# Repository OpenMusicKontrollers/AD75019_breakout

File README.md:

# AD75019 breakout

## About
This is the PCB design of a breakout board for
[Analog Devices](http://www.analog.com)
[AD75019](http://www.analog.com/en/switchesmultiplexers/analog-crosspoint-switches/ad75019/products/product.html) 16x16 analog crosspoint switch.

## Prerequisites
To be used with [KiCAD](http://www.kicad-pcb.org).

## License
This is open source hardware and licensed under [CERN OHL v.1.2](http://ohwr.org/cernohl).

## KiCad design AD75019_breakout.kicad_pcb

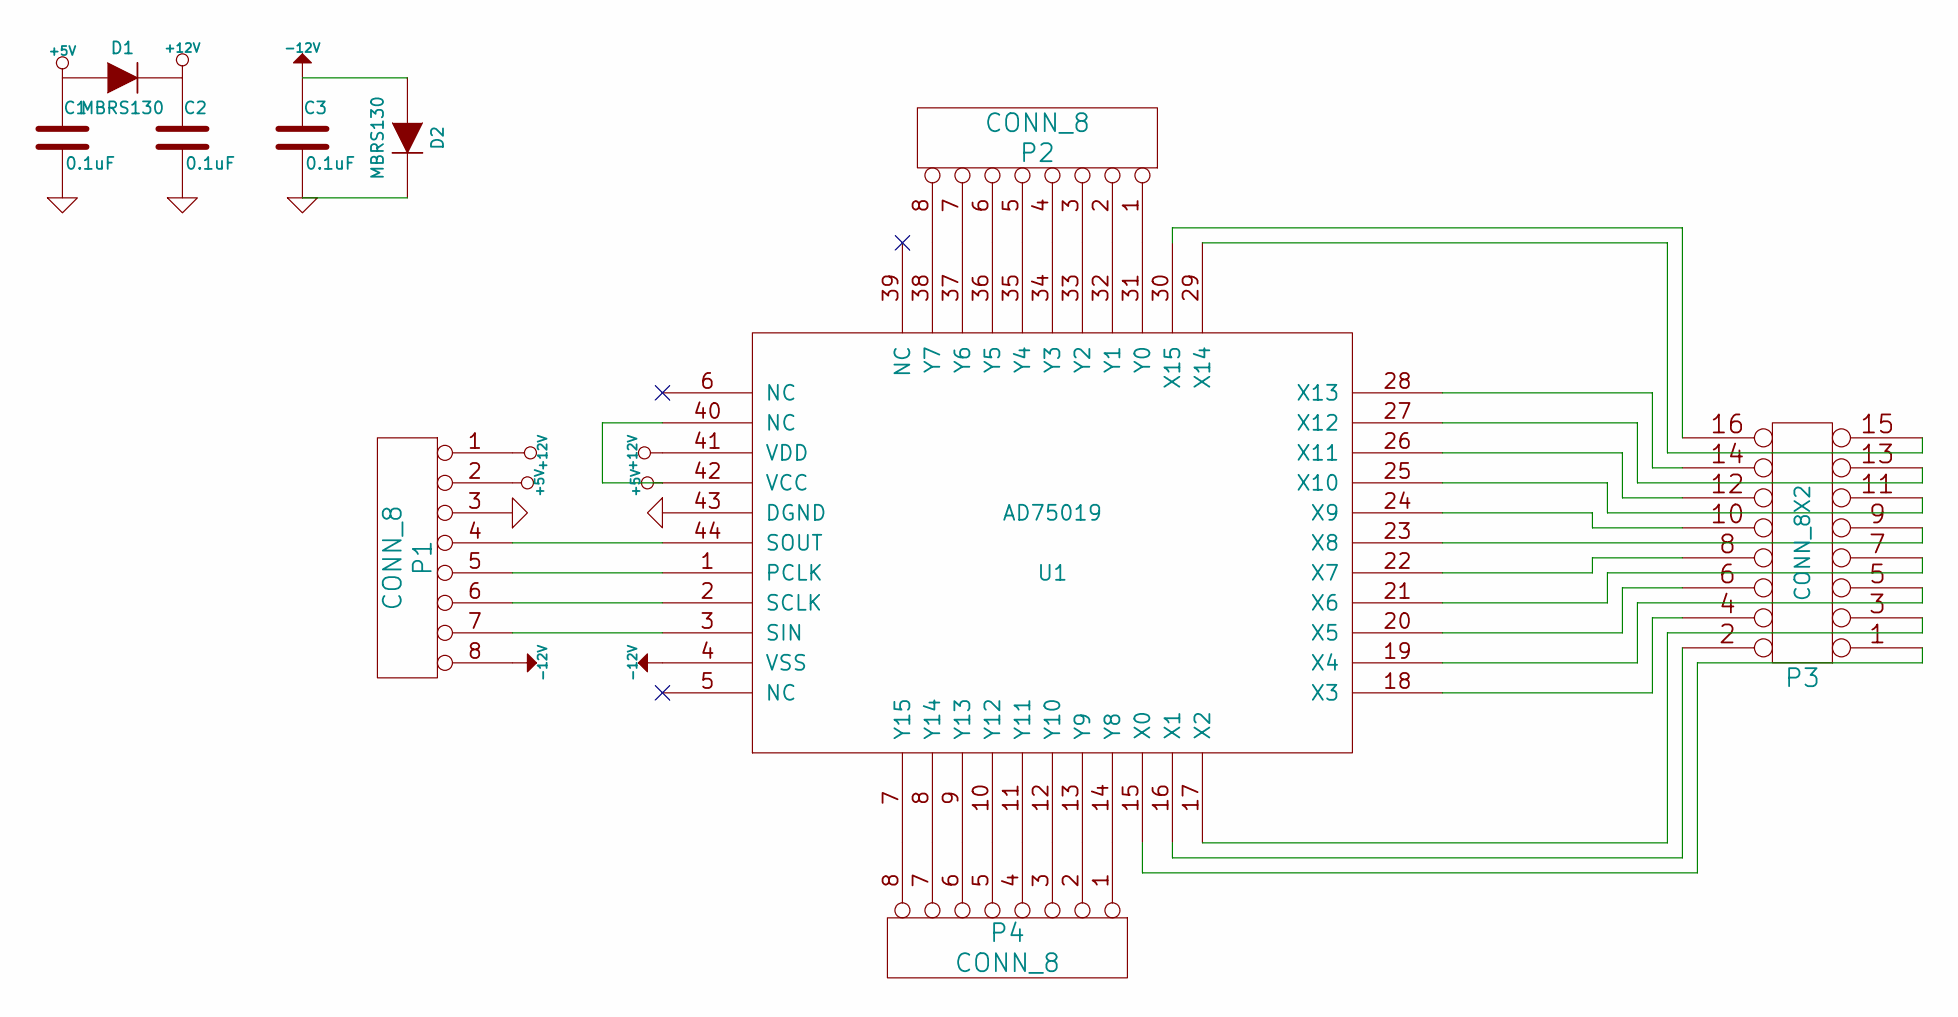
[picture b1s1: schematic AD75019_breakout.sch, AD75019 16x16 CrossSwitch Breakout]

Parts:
C1, C2, C3: 0.1uF; Digi-Key 445-1314-1-ND
D1, D2: MBRS130; Digi-Key MBRS130FSCT-ND
P1, P2, P4: CONN_8
P3: CONN_8X2
U1: AD75019; MODULE; Digi-Key AD75019JPZ-ND

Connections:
+5V: C1.1, D1.1 (A), P1.2, U1.40 (NC), U1.42 (VCC)
+12V: C2.1, D1.2 (K), P1.1, U1.41 (VDD)
-12V: C3.1, D2.1 (A), P1.8, U1.4 (VSS)
GND: C1.2, C2.2, C3.2, D2.2 (K), P1.3, U1.43 (DGND)
unnamed: P3.6, U1.20 (X5)
unnamed: P3.1, U1.15 (X0)
unnamed: P3.4, U1.18 (X3)
unnamed: P3.5, U1.19 (X4)
unnamed: P3.7, U1.21 (X6)
unnamed: P3.8, U1.22 (X7)
unnamed: P1.4, U1.44 (SOUT)
unnamed: P1.5, U1.1 (PCLK)
unnamed: P3.10, U1.24 (X9)
unnamed: P3.13, U1.27 (X12)
unnamed: P3.12, U1.26 (X11)
unnamed: P3.11, U1.25 (X10)
unnamed: P1.6, U1.2 (SCLK)
unnamed: P3.9, U1.23 (X8)
unnamed: P3.3, U1.17 (X2)
unnamed: P3.2, U1.16 (X1)
unnamed: P2.3, U1.33 (Y2)
unnamed: P1.7, U1.3 (SIN)
unnamed: P4.1, U1.14 (Y8)
unnamed: P4.2, U1.13 (Y9)
unnamed: P4.3, U1.12 (Y10)
unnamed: P4.4, U1.11 (Y11)
unnamed: P4.5, U1.10 (Y12)
unnamed: P4.6, U1.9 (Y13)
unnamed: P4.7, U1.8 (Y14)
unnamed: P4.8, U1.7 (Y15)
unnamed: P2.1, U1.31 (Y0)
unnamed: P2.2, U1.32 (Y1)
unnamed: P2.4, U1.34 (Y3)
unnamed: P2.5, U1.35 (Y4)
unnamed: P2.6, U1.36 (Y5)
unnamed: P2.7, U1.37 (Y6)
unnamed: P2.8, U1.38 (Y7)
unnamed: P3.16, U1.30 (X15)
unnamed: P3.14, U1.28 (X13)
unnamed: P3.15, U1.29 (X14)

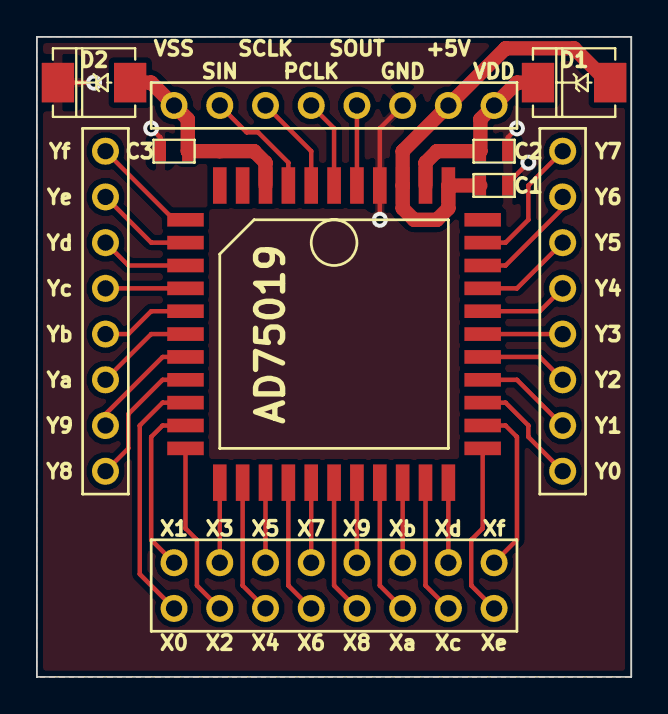
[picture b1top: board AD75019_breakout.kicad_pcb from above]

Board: 2 copper layers, 33.0 x 35.6 mm, 10 parts (0 on the bottom side), 40 nets.

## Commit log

2013-11-25 polished W5500 integration, add AD75019
2013-12-17 AD75019 Rev2. case exploded labels.
2014-03-02 solder paste clearence for 125um mylar stencils
2014-03-02 add README.md and licensing
2014-03-02 path fixes after repo split

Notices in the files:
AD75019_breakout.kicad_pcb:
Copyright (c) 2013 Hanspeter Portner (dev@open-music-kontrollers.ch)
